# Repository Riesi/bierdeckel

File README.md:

# Introduction
This is the implementation of an open hardware smart beer coaster.
As a core principle the beer coaster is simply a battery powered scale with LEDs and BLE.
These components enable a variety of interesting applications that can be implemented on top of the provided hardware.

## Default app
Currently the default app implementation is a hardcoded rainbow pattern, which gets dimmed relative to the analog input value of the force sensor's measurement. Due to part to part variance on the assembled PCBs the analog values can be different, which means the internal thresholds have to be adapted between PCBs.

## Electro-Mechanical Core Principle
The core component to allow for weight measurements is the piezo-electric force sensor. This sensor translates the force transferred from the coaster's feet into an electric signal, which can be used by the ESP32-C3 microcontroller.

# Code
The code is written in Rust and built with the Rust toolchain provided by Espressif. **It is highly recommended to use Linux for building the code**. The Windows version of the tools needed have some issues, which will make it a lot harder or almost impossible to build the project.

## Setup
There are a few things to install to properly build and flash the firmware onto the device. 
First and foremost the general Rust tooling has to be installed. This means installing `rustup` and making sure `cargo` is working.

### Quickstart on Arch
On Arch you can simply install `rustup`, `espup` and `espflash` via the package manager. You still need to run the toolchain downloads/installs, but you dont have to build anything.
```
sudo pacman -S base-devel rustup espup espflash
rustup default stable
espup install
```
### ESP Toolchain
For the ESP toolchain one has to follow the installation and quickstart guide on the `espup` repository.

https://github.com/esp-rs/espup?tab=readme-ov-file#installation

### Flash Tool
To flash the built firmware the `espflash` tool is needed:

https://github.com/esp-rs/espflash/blob/main/cargo-espflash/README.md#installation

## Building
If everything got properly installed and configured in the previous steps, to build the code one has to simply call:

```
cargo build
```

## Flashing
To build and flash the firmware onto the microcontroller the following command is needed:

```
cargo espflash flash -B 115200 --partition-table partitions.csv --erase-parts ota_1
```

### OTA
The reference beer coaster code implements an OTA update scheme with A/B partitioning.
To generate a OTA-image you simply have to run:

```
espflash save-image --chip esp32c3 target/riscv32imc-esp-espidf/debug/beercoaster beercoaster.bin
```

After this you have to copy the `beercoaster.bin` file into the `bt_flasher` folder and run the flasher with:
```
cargo run
```

## Serial
To connect to the serial interface of the beer coaster this command can be used:
```
espflash  monitor -p /dev/ttyUSB0 -B 115200
```

# PCB Design
The PCB is designed with KiCad. The project should contain all the components to work with it.
When ordering the current version a 1.6mm thick single layer PCB is required, due to assumptions from the mechanical base plate.

# Mechanical
This part of the project is done in FreeCAD and consists of 2 parts which act as the housing for the PCB. The mechanical parts are designed to be 3d printable. The base clips onto the PCB and holds itself in place. 
The key feature of the mechanical design are thin membrane sections, which allow these sections of the base plate to elastically deform. This enables the actuation of buttons on the PCB and the pressure sensor for the weight measurement.

## Material
The design has been tested with PET and ASA, but you can use anything that is:
* water resistant
* doesn't degrade under cyclical deformation
* allows for enough flex to actuate buttons and the pressure sensor

## Assembly Water Tightness
* It is recommended to use silicone to seal the sides of the assembly from water ingress.
* The center LED has to be covered with clear resin to prevent water from getting in.

## BoM
| Part | Amount |
| ---  | ---    |
| Base | 1      |
| Foot | 4      |

# Calculations
Contains some files with related calculations for the PCB design. 

# Licensing
The different parts of the beer coaster require different licenses, due to the licenses only covering for example either code or hardware. For this reason the repository contains different licenses. Each subfolder contains the appropriate license for all files and subfolders within.
The current licenses used are:
* GPL-3.0
* CERN-OHL-S-2.0
* Beerware

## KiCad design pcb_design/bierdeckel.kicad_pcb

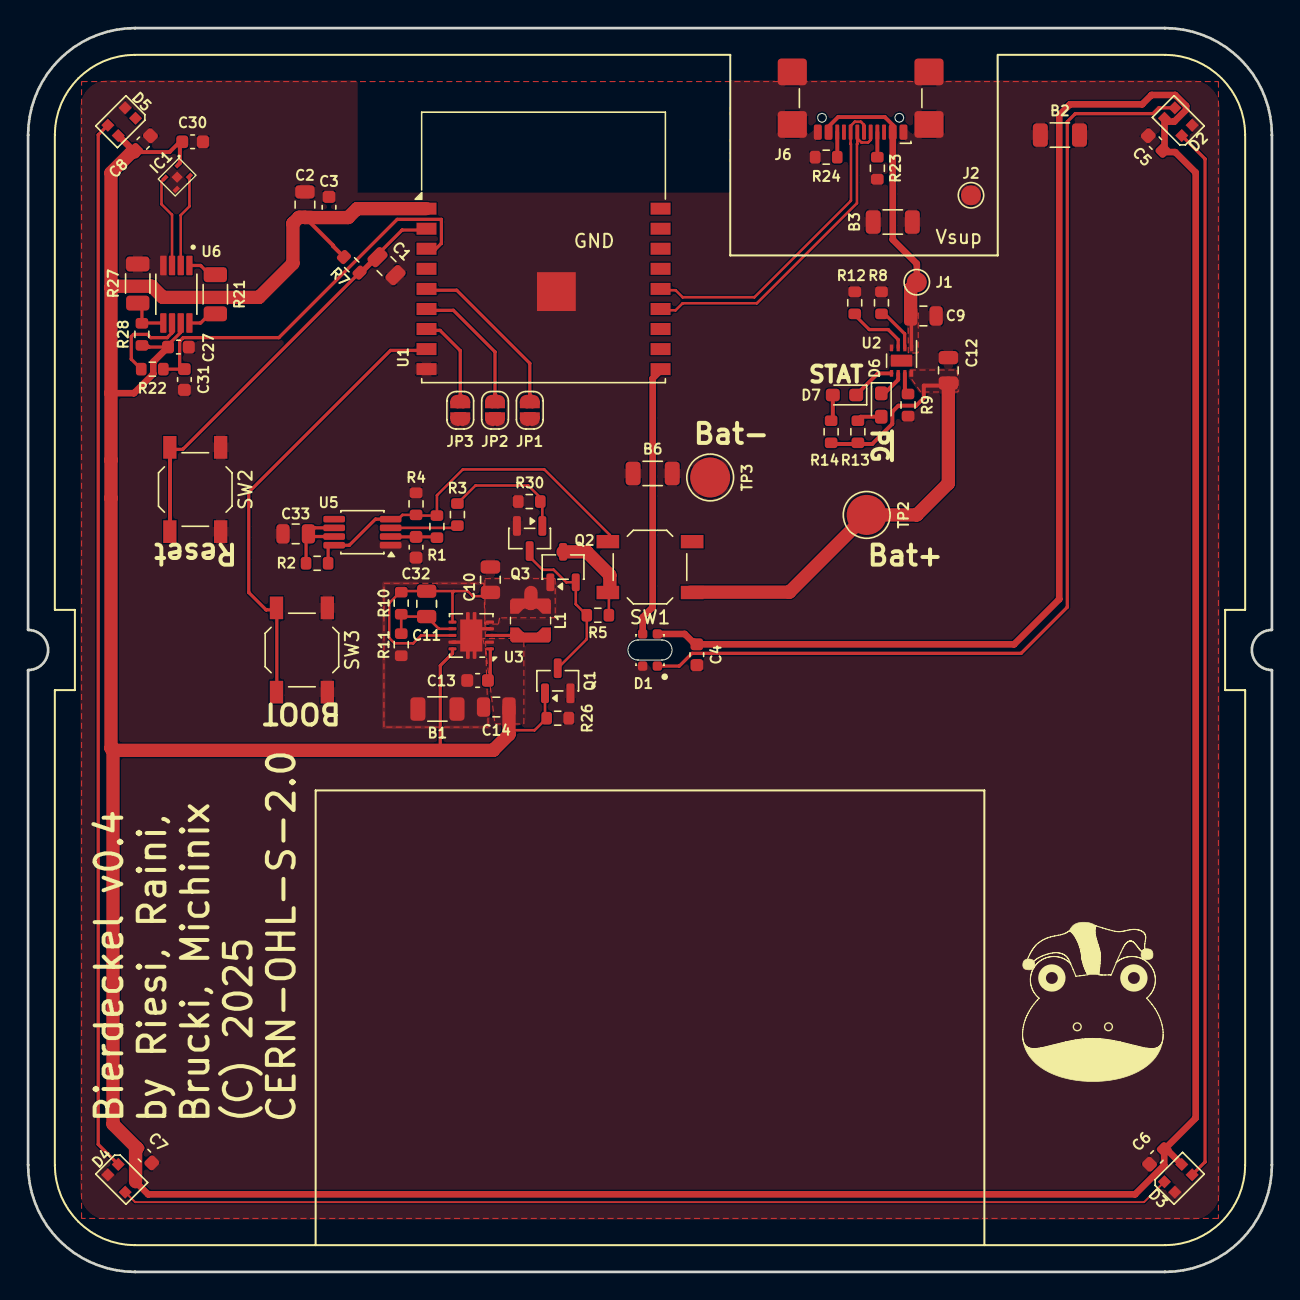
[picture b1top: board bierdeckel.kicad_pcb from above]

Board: 2 copper layers, 93.0 x 93.0 mm, 72 parts (0 on the bottom side), 42 nets.

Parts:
B1, B2, B3, B6: 0R; R_1206_3216Metric
C1, C9, C11, C12: 1uF; C_0805_2012Metric
C2, C10, C14, C33: 10uF; C_0805_2012Metric
C3, C4, C5, C6, C7, C8, C13, C27, C30, C31, C32: 0.1uF; C_0603_1608Metric
D1: WS2812B 2020; ws2812B_2020_flipped
D2, D3, D4, D5: WS2812B-2020; LED_WS2812B-2020_PLCC4_2.0x2.0mm
D6: XL-1608UBC-04; LED_0603_1608Metric_Pad1.05x0.95mm_HandSolder
D7: A-SP192DGHC-C01-4T; LED_0603_1608Metric_Pad1.05x0.95mm_HandSolder
IC1: HSFPAR004A
J1, J2: Pogo; TestPoint_Pad_D1.5mm
J6: USB-TYPE-C-020; USB_C_Receptacle_GCT_USB4110
JP1: A0; SolderJumper-2_P1.3mm_Open_RoundedPad1.0x1.5mm
JP2: A1; SolderJumper-2_P1.3mm_Open_RoundedPad1.0x1.5mm
JP3: A2; SolderJumper-2_P1.3mm_Open_RoundedPad1.0x1.5mm
L1: 2.2µH LPS3015-222MRC; LPS3015-222MRC
Q1, Q3: BSS123; SOT-23
Q2: SP20P18T1; SOT-23-3
R1, R3, R8: 620; R_0603_1608Metric
R2, R5, R11, R30: 200k; R_0603_1608Metric
R4, R7, R12, R13, R14, R28: 10k; R_0603_1608Metric
R9: 27k4; R_0603_1608Metric
R10, R26: 2.2M; R_0603_1608Metric
R21: 4k02; R_1206_3216Metric
R22, R23, R24: 5k1; R_0603_1608Metric
R27: 3k; R_1206_3216Metric
SW1, SW2, SW3: PTS526 SK15 SMTR2 LFS; SW_SPST_TL3342
TP2, TP3: TestPoint; TestPoint_Pad_D3.0mm
U1: ESP32-C3-WROOM-02
U2: BQ25176J; WSON-8-1EP_2x2mm_P0.5mm_EP0.9x1.6mm_ThermalVias
U3: TPS61201DRC; Texas_S-PVSON-N10_ThermalVias
U5: LMC555xMM; VSSOP-8_3x3mm_P0.65mm
U6: INA317IDGKR; INA317IDGKR_SOP65P490X110-8N

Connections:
+3.3V: C2.1, C3.1, C4.1, C5.1, C6.1, C7.1, C8.1, C14.1, C27.1, C30.1, D1.4 (VDD), D2.4 (VDD), D3.4 (VDD), D4.4 (VDD), D5.4 (VDD), IC1.1 (VDD), Q1.1 (G), R7.1, R26.1, R28.2, U1.1 (3V3), U3.2 (VOUT), U3.10 (FB), U6.7 (V+)
+BATT: C10.1, C11.1, L1.1, Q2.1 (D), R10.1, U3.5 (VIN), U3.6 (EN), U3.8 (PS)
+BATT_EXT: C12.1, Q2.3 (S), R5.1, R13.1, R14.1, SW1.1, TP2.1 (1_1), U2.8 (OUT)
/AD0: JP1.1 (A), U1.5 (IO6)
/AD1: JP2.1 (A), U1.6 (IO7)
/AD2: JP3.1 (A), U1.7 (IO8)
/LED_DATA: D1.3 (DIN), U1.10 (IO10)
/NE_TOGGLE_OUT: Q3.1 (G), R3.1, R30.1
/Pressure Gauge/VR+: IC1.4 (V1), U6.3 (VIN+)
/Pressure Gauge/VR-: IC1.2 (V2), U6.2 (VIN-)
/Pressure Gauge/Vref: R27.1, R28.1, U6.5 (REF)
/RST: C1.1, R7.2, SW2.2, U1.2 (EN)
/USB+: J6.A6 (D+), J6.B6 (D+), U1.14 (IO19)
/USB-: J6.A7 (D-), J6.B7 (D-), U1.13 (IO18)
/Vcharge: C9.1, J1.1 (1_1), J6.A4 (VBUS), J6.A9 (VBUS), J6.B4 (VBUS), J6.B9 (VBUS), U2.1 (IN)
/Vpress: C31.1, R22.1, U1.3 (IO4)
/~BOOTLOADER: SW3.2, U1.8 (IO9)
GND: B1.1 (A), B1.2 (B), B2.1 (A), B2.2 (B), B3.1 (A), B3.2 (B), B6.1 (A), B6.2 (B), C1.2, C2.2, C3.2, C4.2, C5.2, C6.2, C7.2, C8.2, C9.2, C10.2, C12.2, C13.2, C14.2, C27.2, C30.2, C31.2, C32.2, C33.2, D1.2 (VSS), D2.2 (VSS), D3.2 (VSS), D4.2 (VSS), D5.2 (VSS), IC1.3 (GND_1), IC1.5 (GND_2), J2.1 (1_1), J6.A1 (GND), J6.A12 (GND), J6.B1 (GND), J6.B12 (GND), J6.SH (SHIELD), JP1.2 (B), JP2.2 (B), JP3.2 (B), Q1.2 (S), Q3.2 (S), R4.1, R8.2, R9.2, R11.2, R12.1, R23.2, R24.2, R26.2, R27.2, R30.2, SW2.1, SW3.1, TP3.1 (1_1), U1.9 (GND), U1.19 (GND), U2.4 (GND), U3.4 (PGND), U3.9 (GND), U3.11 (PAD), U5.1 (GND), U6.4 (V_)
unnamed: D1.1 (DOUT), D2.3 (DIN)
unnamed: D2.1 (DOUT), D3.3 (DIN)
unnamed: D3.1 (DOUT), D4.3 (DIN)
unnamed: D4.1 (DOUT), D5.3 (DIN)
unnamed: D6.2 (A), R13.2
unnamed: D6.1 (K), U2.6 (~PG)
unnamed: D7.2 (A), R14.2
unnamed: D7.1 (K), U2.5 (STAT)
unnamed: J6.A5 (CC1), R23.1
unnamed: J6.B5 (CC2), R24.1
unnamed: Q1.3 (D), Q2.2 (G), Q3.3 (D), R5.2
unnamed: R8.1, U2.2 (ISET)
unnamed: R12.2, U2.3 (TS)
unnamed: R9.1, U2.7 (VSET)
unnamed: L1.2, U3.3 (L)
unnamed: C11.2, R10.2, R11.1, U3.7 (UVLO)
unnamed: C13.1, U3.1 (VAUX)
unnamed: C33.1, R2.1, U5.6 (THRES), U5.7 (DISCH)
unnamed: R3.2, U5.3 (OUT)
unnamed: C32.1, R1.1, U5.2 (TRIG)
unnamed: R1.2, R2.2, R4.2, SW1.2, U5.4 (~RST), U5.8 (VCC)
unnamed: R21.2, U6.1 (RG)
unnamed: R21.1, U6.8 (RG__1)
unnamed: R22.2, U6.6 (VOUT)

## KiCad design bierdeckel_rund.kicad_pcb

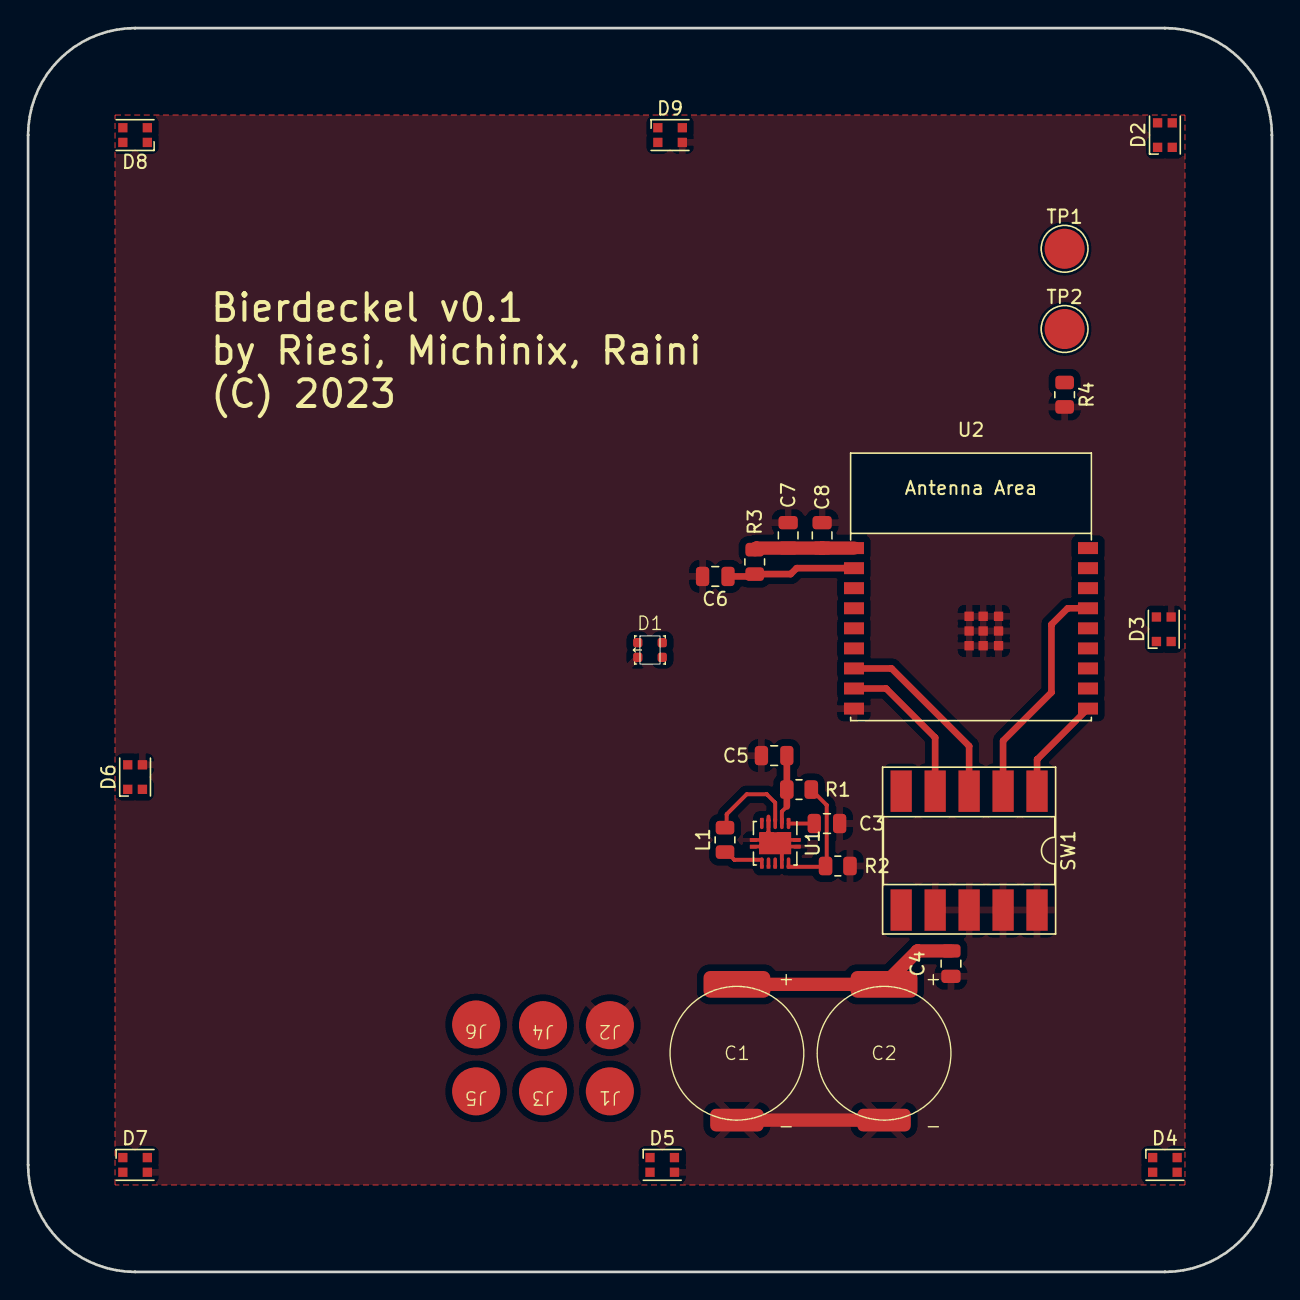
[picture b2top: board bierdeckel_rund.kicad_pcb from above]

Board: 2 copper layers, 93.0 x 93.0 mm, 33 parts (0 on the bottom side), 26 nets.

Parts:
C1, C2: 330mF; super_cap
C3, C8: 0.1uF; C_0805_2012Metric
C4, C5, C7: 10uF; C_0805_2012Metric
C6: 1uF; C_0805_2012Metric
D1: WS2812B 2020 Flipped; ws2812B_2020_flipped
D2, D3, D4, D5, D6, D7, D8, D9: WS2812B; LED_WS2812B-2020_PLCC4_2.0x2.0mm
J1, J2, J3, J4, J5, J6: pogo_receptor
L1: 2.2µH; R_0805_2012Metric
R1, R2: R; R_0805_2012Metric
R3, R4: 10k; R_0805_2012Metric
SW1: Adress Coding; DIP-10_W8.89mm_SMDSocket_LongPads
TP1, TP2: TestPoint; TestPoint_Pad_D3.0mm
U1: TPS61201DRC; Texas_S-PVSON-N10_ThermalVias
U2: ESP32-C3-WROOM-02

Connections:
+3.3V: C5.1, C7.1, C8.1, D1.1 (VDD), D2.1 (VDD), D3.1 (VDD), D4.1 (VDD), D5.1 (VDD), D6.1 (VDD), D7.1 (VDD), D8.1 (VDD), D9.1 (VDD), R1.1, R3.1, TP1.1, U1.2 (VOUT), U2.1 (3V3)
/AD0: SW1.3, U2.7 (GPIO8)
/AD1: SW1.4, U2.8 (GPIO9)
/AD2: SW1.1, U2.10 (GPIO10)
/AD3: SW1.2, U2.15 (GPIO3/ADC1_CH3)
/LED_DATA: D1.4 (DIN), U2.12 (GPIO21/U0TXD)
/TCK: J5.1 (pogo_receptor), U2.5 (GPIO6)
/TDI: J4.1 (pogo_receptor), U2.4 (GPIO5/ADC2_CH0)
/TDO: J6.1 (pogo_receptor), U2.6 (GPIO7)
/TMS: J3.1 (pogo_receptor), U2.3 (GPIO4/ADC1_CH4)
/Vcap: C1.1, C2.1, C4.1, J1.1 (pogo_receptor), SW1.6
/Vpress: R4.1, TP2.1, U2.16 (GPIO2/ADC1_CH2)
/Vreg_in: L1.1, SW1.5, U1.5 (VIN), U1.6 (EN), U1.7 (UVLO), U1.8 (PS)
GND: C1.2, C2.2, C3.2, C4.2, C5.2, C6.2, C7.2, C8.2, D1.3 (VSS), D2.3 (VSS), D3.3 (VSS), D4.3 (VSS), D5.3 (VSS), D6.3 (VSS), D7.3 (VSS), D8.3 (VSS), D9.3 (VSS), J2.1 (pogo_receptor), R2.2, R4.2, SW1.7, SW1.8, SW1.9, SW1.10, U1.4 (PGND), U1.9 (GND), U1.11 (PAD), U2.9 (GND), U2.19 (GND)
unnamed: D1.2 (DOUT), D2.4 (DIN)
unnamed: D2.2 (DOUT), D3.4 (DIN)
unnamed: D3.2 (DOUT), D4.4 (DIN)
unnamed: D4.2 (DOUT), D5.4 (DIN)
unnamed: D5.2 (DOUT), D6.4 (DIN)
unnamed: D6.2 (DOUT), D7.4 (DIN)
unnamed: D7.2 (DOUT), D8.4 (DIN)
unnamed: D8.2 (DOUT), D9.4 (DIN)
unnamed: R1.2, R2.1, U1.10 (FB)
unnamed: L1.2, U1.3 (L)
unnamed: C3.1, U1.1 (VAUX)
unnamed: C6.1, R3.2, U2.2 (EN/CHIP_PU)

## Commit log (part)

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2023-10-13 initial design and code drop
2024-03-10 Implement Simon's layout suggestions
2024-05-01 remove ATTiny; fix LED footprints; start cleanup
2024-05-03 improve layout further
2024-05-22 fix battery charging IC circuit missing TS pulldown
2024-05-26 fix some layout issues
2024-05-26 set new LED pin
2024-05-27 correct buck/boost bootstrap circuit to handle falling/rising hysteresis on Uvlo
2024-05-27 give PCB a title
2024-05-29 improve buck/boost footprint based on datasheet
2024-05-29 improve edge marker, get rid of 1 power bridge
2024-05-29 update version number
2024-05-29 improve solder paste masking
2024-05-30 improve routing
2024-05-30 change pressure bridge to four DMS
2024-06-02 add nudge into edge cut; improve routing and wheat stone bridge position
2024-06-02 add an example lipo as user comment
2024-06-06 change to 2 pressure gauge strips
2024-06-06 remove other PCB shapes
2024-07-25 update design; add 3d models to everything; add notches to PCB
2024-07-25 reannotate components and move some designators
2024-10-17 add test code for python and rust BT OTA flasher tool
2024-10-24 implement proper flashing and first image verification
2024-11-17 code drop BT firmware with LED example
2024-11-17 clean up
2024-11-17 get rid of python and C code
2024-11-17 drop deep sleep example code
2024-11-17 update design
2024-12-22 add a few animation patterns as a test
2024-12-22 add TODOs and clamp input delay time to u8::MAX
2024-12-22 add color constants
2024-12-22 cleanup led pattern code
2024-12-23 add function to automatically create led shift rotations and use it
2024-12-23 add more colors and use them in rainbow animation
2024-12-23 add more colors
2024-12-23 add yellow blinking
2024-12-23 implement simple flash feedback
2024-12-25 begin implementing event queue
2024-12-27 set fixed cc version and toolchain channel to make project better portable
2024-12-27 improve minimum cycle code
2024-12-28 fix output unit in bt flasher
2024-12-28 fix watchdog timeout error due to empty main loop
2024-12-28 add error pattern to failure transition
2024-12-30 implement ADC mwe
2024-12-31 begin refactor flasher
2024-12-31 refactor ESP uuids
2024-12-31 refactor BT flasher tool to event driven logic for robust validation
2024-12-31 configure adc and improve output
2025-01-05 implement brightness scaling via ADC
2025-01-17 use single value channel for adc
2025-01-19 implement glass scale feature
2025-01-19 increase BT timeout for verification
2025-01-19 fix brightness initial value
2025-01-19 change curve
2025-01-20 add linear 3 part brightness curve
2025-01-20 fix less than empty weight to zero and clean up code
2025-02-01 bump versions and use upstream esp-ota
2025-02-01 bump dependencies and fix compilation
2025-02-01 remove local copy of esp-ota
2025-02-13 add Kicad CI
2025-02-13 fix ERC and DRC
2025-02-13 fix ERC
2025-02-15 update HAL IDF and dependencies
2025-03-18 update to kicad 9.0 and place Qi-charge IC
2025-03-20 continue Qi-Charge circuit
2025-03-31 implement initial power latching idea
2025-04-01 update pcb file and fix a few silkscreen overlaps
2025-04-02 continue Qi-Charger work
2025-05-21 start qi charge impl
2025-06-13 start reshuffeling for qi-charge version
2025-07-14 before gauge replacement
2025-07-14 initial piezo resistive IC impl
2025-07-15 continue new pressure sensor implementation
2025-07-16 continue routing
2025-07-17 continue refactor
2025-07-17 further work
2025-07-24 before USB connector
2025-07-24 add usb c connector
2025-07-24 remove excessive ESP mini
2025-07-24 finish up routing and fix latching
2025-07-29 replace some components for JLC order
2025-07-29 change some more components to LCSC ones
2025-07-30 start implementing mechanical base
2025-08-04 update PCB usb position and further base work
2025-08-06 implement more parts of the base
2025-08-07 further mechanical work
2025-08-14 reposition buttons and finish up initial base design
2025-08-18 further base work
2025-08-18 update base designs
2025-09-02 add 555 based power latching
2025-09-02 route power latch circuit
2025-09-04 prepare for ordering
2025-09-04 add unit to capacitor value
2025-09-23 minor adjustments of coaster base
2025-09-23 increase lipo holder length
2025-09-27 get rid of unused variables
2025-09-27 fix command parameter change for flashing
2025-09-29 bump some dependency versions; pin compiler version; remove broken embassy-time-driver dep
2025-09-30 fix adc readout logic for piezo pressure sensor
2025-10-06 fix: change ADC config to use factory curve
2025-10-06 begin improving power latching circuit
2025-10-06 disable embassy-timer-driver due to being broken with current toolchains
2025-10-07 move peripheral code
2025-10-07 run rustfmt
2025-10-11 change power ON and latching circuit to use FETs
    should reduce leakage currents :)
2025-10-11 add initial BT log code
2025-10-11 add info in license to PCB design
2025-10-11 move PCB files into subfolder
2025-10-11 update CI kicad version
2025-10-11 make CI run on CI changes
2025-10-11 move CI file
2025-10-11 set CI config path
2025-10-11 make CI always run on yml changes
2025-10-11 define project files
2025-10-11 Try to fix CI running
2025-10-11 fix filter
2025-10-20 add licensing to components
2025-10-20 add README
2025-10-20 add license to PCB silkscreen
2025-10-20 add 3d models of some components
2025-10-20 update PCB in base CAD file
2025-10-20 add image of the coaster PCB
2025-10-21 regenerate HTML BoM
2025-10-21 fix license warning from cargo
2025-10-21 fix building deep sleep example and cleanup
2025-10-21 add quickstart section for Arch installs
2025-10-21 rename beercoaster main code to make it usage more obvious
2026-02-17 add iced UI example as a flasher gui basis
    lets try this
2026-02-17 start moving bt flasher code to gui as crate
2026-02-18 initial addition of file picker
2026-02-18 try Task system
2026-02-18 implement working async file picker test code
2026-02-19 cleanup
2026-02-20 remove clone
2026-02-20 fix compile
2026-02-22 initial flasher fixes to get example working
2026-02-23 begin adding git describe and read version command
2026-02-24 initial version print via BT
    fix dirty status and simplify version get in gui
2026-02-24 reenable proper flash sequence
2026-03-21 update PCB to Kicad 10
2026-03-21 update CI
2026-03-22 vendor more symbols
2026-03-22 add ignore for new temp files
2026-03-23 add more widgets that will be used in gui
2026-04-06 start initial test code
2026-04-13 fix initial sipper example

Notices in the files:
bierdeckel_rund.kicad_pcb:
(C) 2023
pcb_design/bierdeckel.kicad_pcb:
SPDX-License-Identifier: CERN-OHL-S-2.0
SPDX-FileCopyrightText: 2023-2025 Stefan Riesenberger
